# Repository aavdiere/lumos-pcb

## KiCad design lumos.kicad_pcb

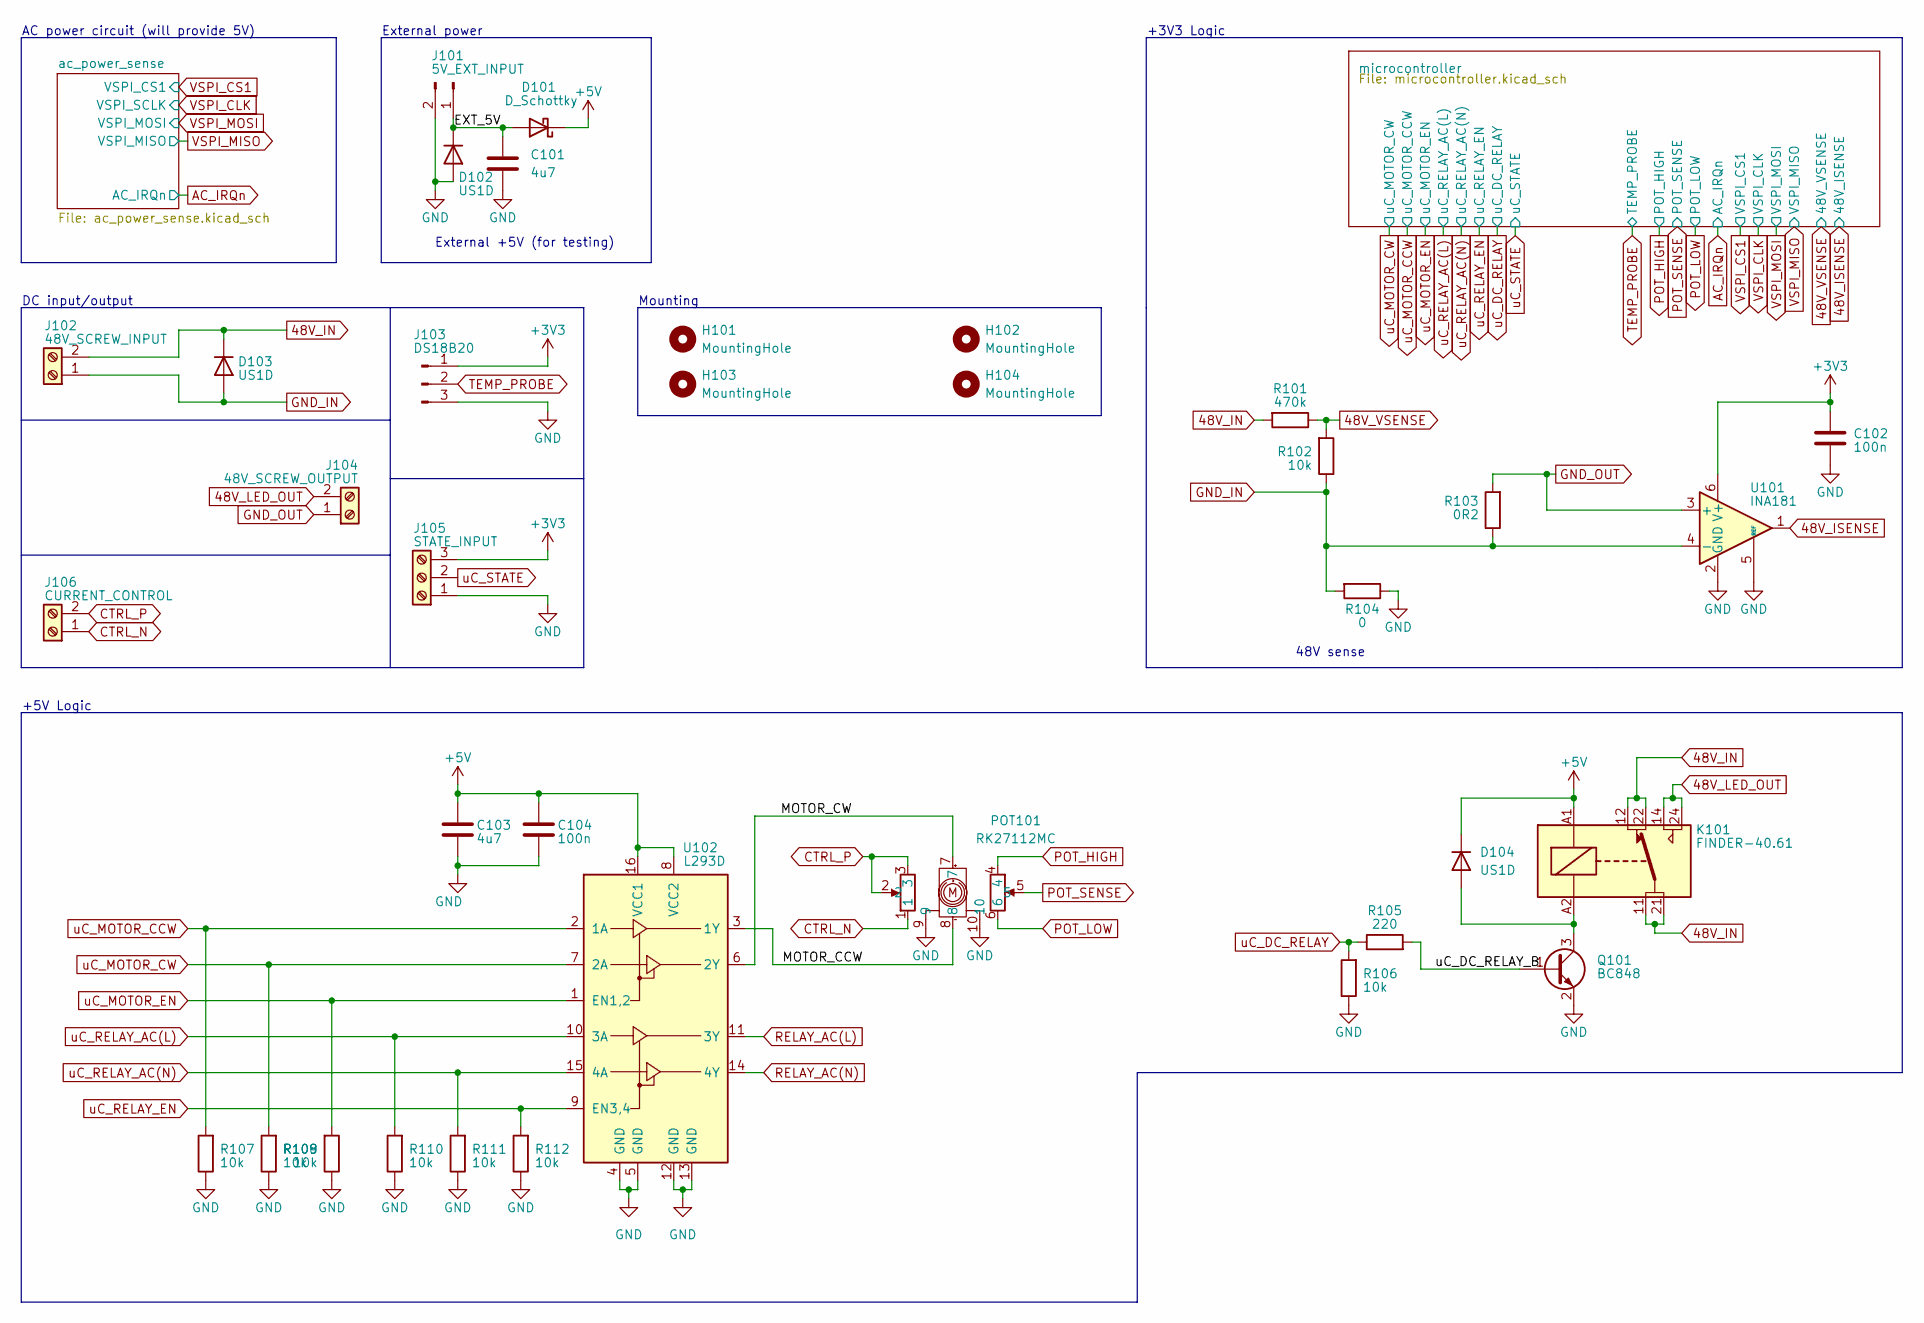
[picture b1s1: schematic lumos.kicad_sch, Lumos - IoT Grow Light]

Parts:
C101, C103: 4u7; C_0402_1005Metric
C102, C104: 100n; C_0402_1005Metric
D101: D_Schottky; D_SOD-523
D102, D103, D104: US1D; D_SMA
H101, H102, H103, H104: MountingHole; MountingHole_3.2mm_M3
J101: 5V_EXT_INPUT; PinHeader_1x02_P2.54mm_Vertical
J102: 48V_SCREW_INPUT; TerminalBlock_Phoenix_MKDS-1,5-2-5.08_1x02_P5.08mm_Horizont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
J103: DS18B20; PinHeader_1x03_P2.54mm_Vertical
J104: 48V_SCREW_OUTPUT; TerminalBlock_Phoenix_MKDS-1,5-2-5.08_1x02_P5.08mm_Horizont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
J105: STATE_INPUT; TerminalBlock_Phoenix_MKDS-1,5-3-5.08_1x03_P5.08mm_Horizont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
J106: CURRENT_CONTROL; TerminalBlock_Phoenix_MKDS-1,5-2-5.08_1x02_P5.08mm_Horizont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
K101: FINDER-40.61; Relay_DPDT_Finder_40.52
POT101: RK27112MC
Q101: BC848; SOT-23
R101: 470k; R_0402_1005Metric
R102, R106, R107, R108, R109, R110, R111, R112: 10k; R_0402_1005Metric
R103: 0R2; R_2512_6332Metric; JLCPCB Part C309535
R104: 0; R_0402_1005Metric
R105: 220; R_0402_1005Metric
U101: INA181; SOT-23-6; JLCPCB Part C2058784
U102: L293D; DIP-16_W7.62mm

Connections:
48V_IN: D103.1 (K), J102.2, K101.11, K101.12, K101.21, K101.22, R101.2
48V_ISENSE: U101.1; also elsewhere on the board
48V_LED_OUT: J104.2, K101.14, K101.24
48V_VSENSE: R101.1, R102.2; also elsewhere on the board
+3V3: C102.1, J103.1, J105.3, U101.6 (V+); also elsewhere on the board
+5V: C103.1, C104.1, D101.1 (K), D104.1 (K), K101.A1, U102.8 (VCC2), U102.16 (VCC1); also elsewhere on the board
/EXT_5V: C101.1, D101.2 (A), D102.1 (K), J101.1
/MOTOR_CCW: POT101.8, U102.3 (1Y)
/MOTOR_CW: POT101.7, U102.6 (2Y)
/uC_DC_RELAY_B: Q101.1 (B), R105.2
CTRL_N: J106.1, POT101.1
CTRL_P: J106.2, POT101.2, POT101.3
GND: C101.2, C102.2, C103.2, C104.2, D102.2 (A), J101.2, J103.3, J105.1, POT101.9, POT101.10, Q101.2 (E), R104.1, R106.1, R107.1, R108.1, R109.1, R110.1, R111.1, R112.1, U101.2 (GND), U101.5 (REF), U102.4 (GND), U102.5 (GND), U102.12 (GND), U102.13 (GND); also elsewhere on the board
GND_IN: D103.2 (A), J102.1, R102.1, R103.1, R104.2, U101.4 (-)
GND_OUT: J104.1, R103.2, U101.3 (+)
unnamed: D104.2 (A), K101.A2, Q101.3 (C)
POT_HIGH: POT101.4; also elsewhere on the board
POT_LOW: POT101.6; also elsewhere on the board
POT_SENSE: POT101.5; also elsewhere on the board
RELAY_AC(L): U102.11 (3Y); also elsewhere on the board
RELAY_AC(N): U102.14 (4Y); also elsewhere on the board
TEMP_PROBE: J103.2; also elsewhere on the board
uC_DC_RELAY: R105.1, R106.2; also elsewhere on the board
uC_MOTOR_CCW: R107.2, U102.2 (1A); also elsewhere on the board
uC_MOTOR_CW: R108.2, U102.7 (2A); also elsewhere on the board
uC_MOTOR_EN: R109.2, U102.1 (EN1,2); also elsewhere on the board
uC_RELAY_AC(L): R110.2, U102.10 (3A); also elsewhere on the board
uC_RELAY_AC(N): R111.2, U102.15 (4A); also elsewhere on the board
uC_RELAY_EN: R112.2, U102.9 (EN3,4); also elsewhere on the board
uC_STATE: J105.2; also elsewhere on the board

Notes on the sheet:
AC power circuit (will provide 5V)
+5V Logic
External +5V (for testing)
+3V3 Logic
48V sense
DC input/output
Mounting
External power

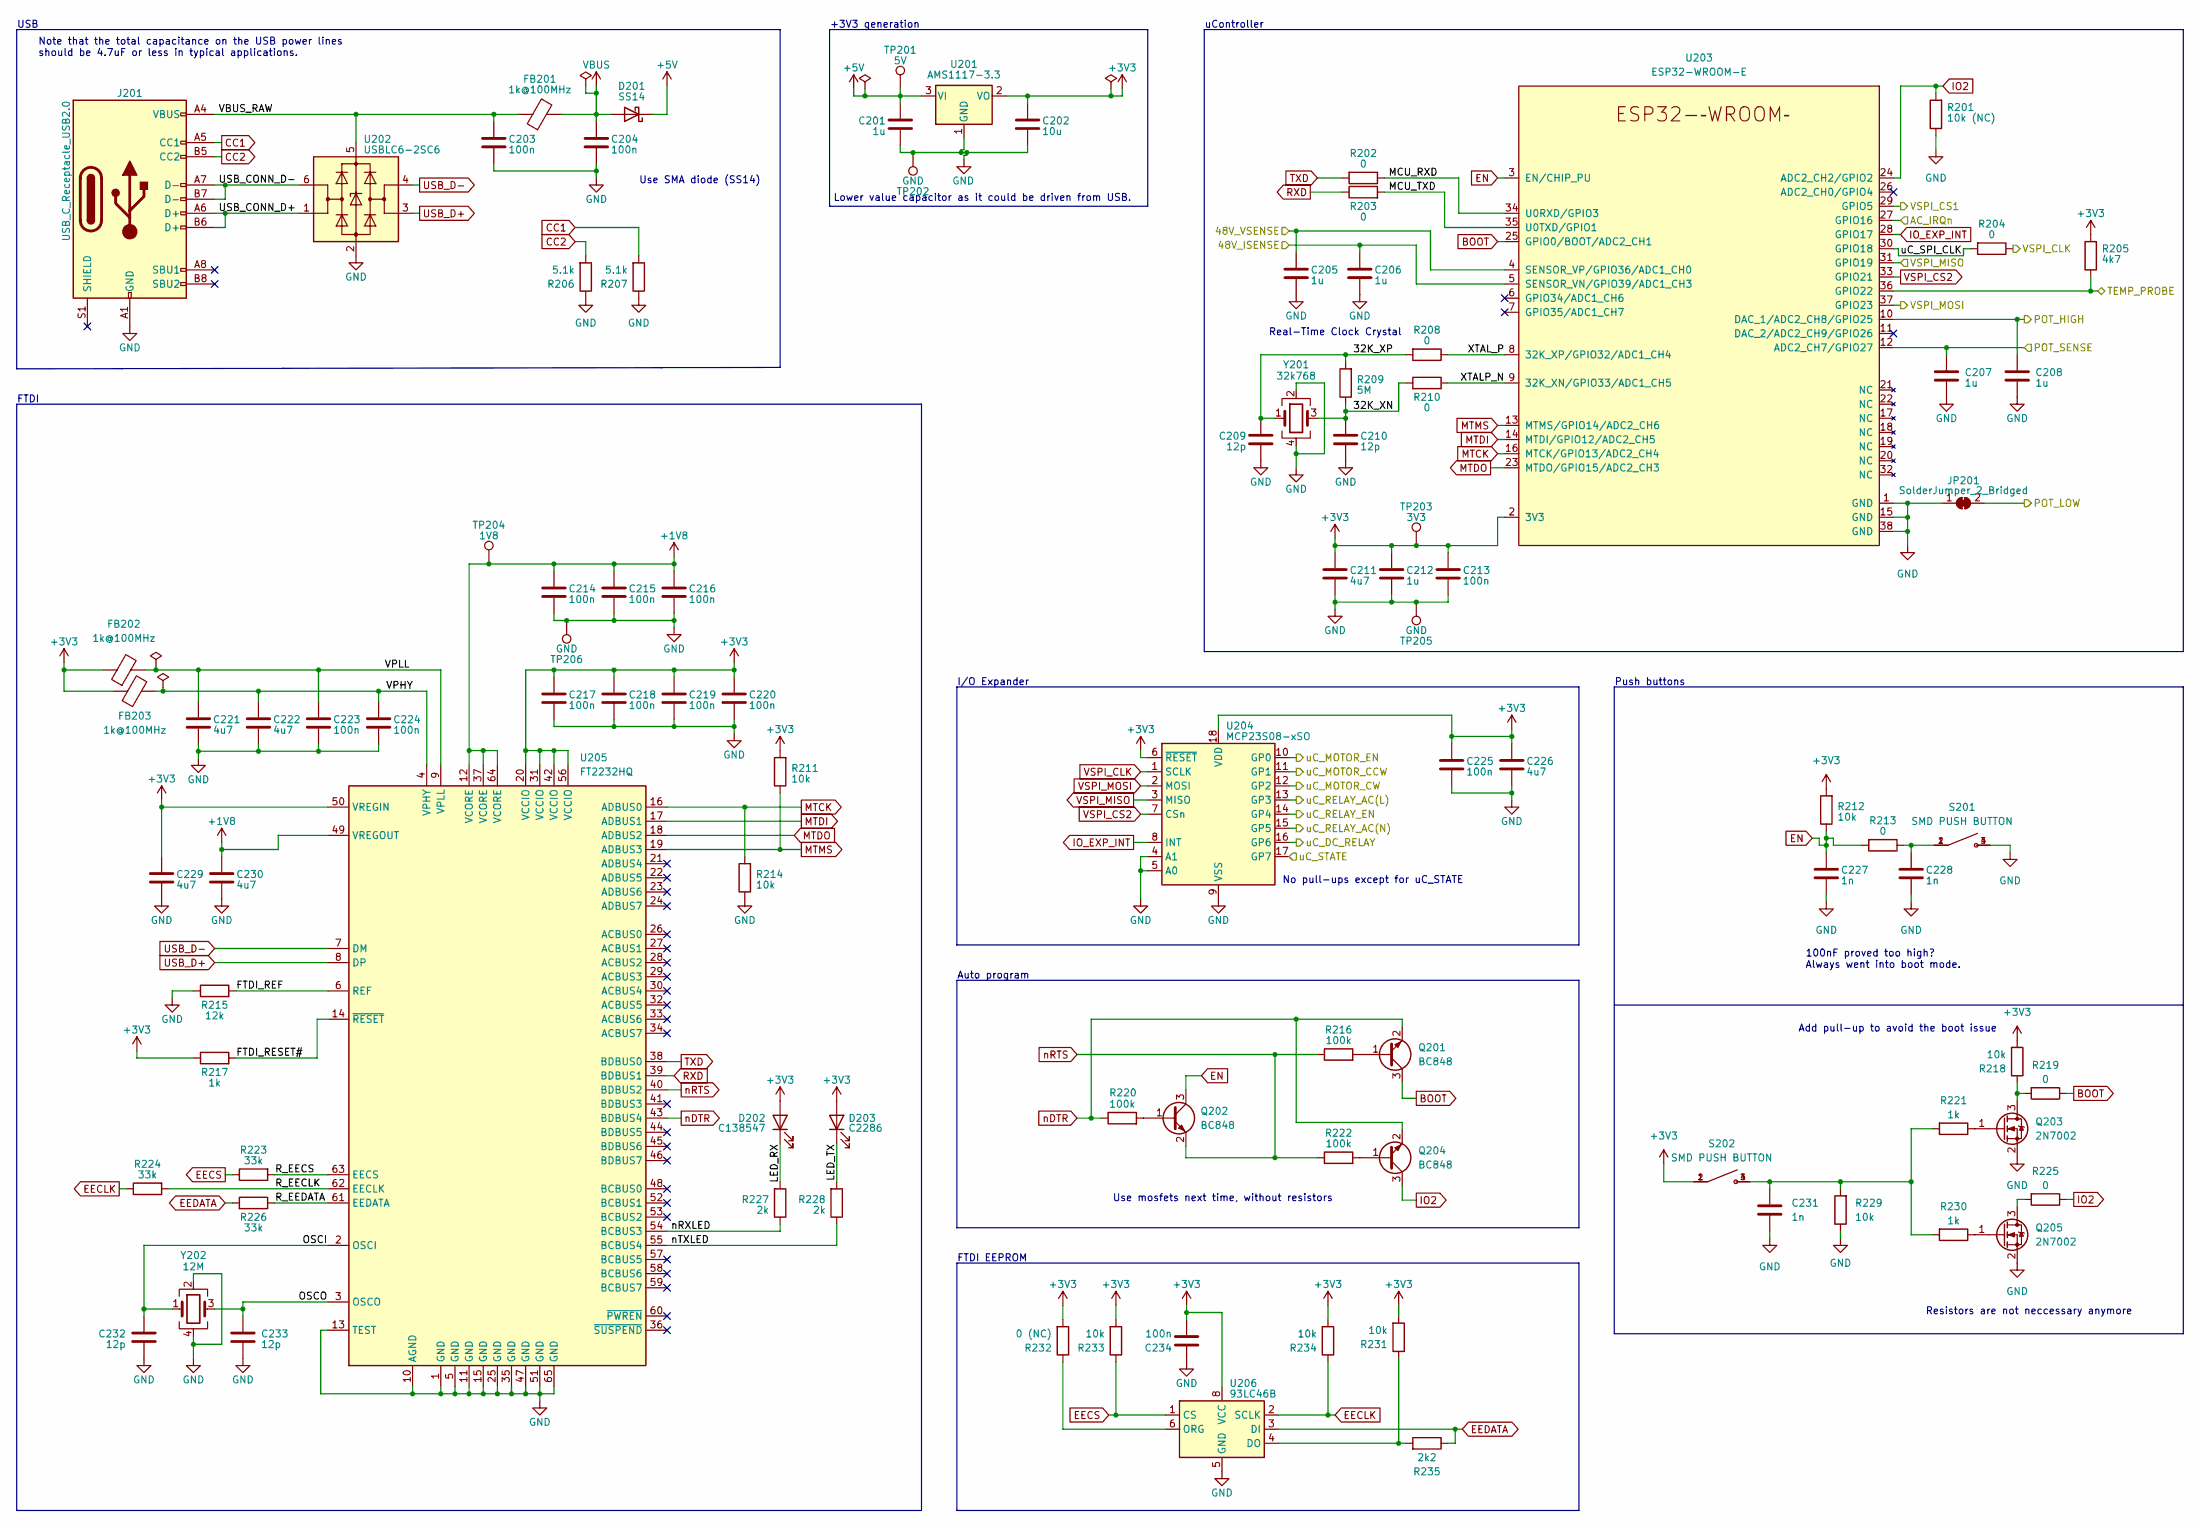
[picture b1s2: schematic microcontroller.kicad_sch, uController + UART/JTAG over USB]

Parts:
C201, C205, C206, C207, C208, C212: 1u; C_0402_1005Metric
C202: 10u; C_0402_1005Metric
C203, C204, C213, C214, C215, C216, C217, C218, C219, C220, C223, C224, C225, C234: 100n; C_0402_1005Metric
C209, C210, C232, C233: 12p; C_0402_1005Metric
C211, C221, C222, C226, C229, C230: 4u7; C_0402_1005Metric
C227, C228, C231: 1n; C_0402_1005Metric
D201: SS14; D_SOD-523
D202: C138547; LED_0603_1608Metric
D203: C2286; LED_0603_1608Metric
FB201, FB202, FB203: 1k@100MHz; L_0402_1005Metric
J201: USB_C_Receptacle_USB2.0; USB_C_Receptacle_HRO_TYPE-C-31-M-12; JLCPCB Part C165948
JP201: SolderJumper_2_Bridged; SolderJumper-2_P1.3mm_Bridged2Bar_Pad1.0x1.5mm
Q201, Q202, Q204: BC848; SOT-23
Q203, Q205: 2N7002; SOT-23
R201: 10k (NC); R_0402_1005Metric
R202, R203, R204, R208, R210, R213, R219, R225: 0; R_0402_1005Metric
R205: 4k7; R_0402_1005Metric
R206, R207: 5.1k; R_0402_1005Metric
R209: 5M; R_0402_1005Metric
R211, R212, R214, R218, R229, R231, R233, R234: 10k; R_0402_1005Metric
R215: 12k; R_0402_1005Metric
R216, R220, R222: 100k; R_0402_1005Metric
R217, R221, R230: 1k; R_0402_1005Metric
R223, R224, R226: 33k; R_0402_1005Metric
R227, R228: 2k; R_0402_1005Metric
R232: 0 (NC); R_0402_1005Metric
R235: 2k2; R_0402_1005Metric
S201, S202: SMD PUSH BUTTON; SW_2-1437565-9; PARTREV V
TP201: 5V; TestPoint_Pad_D2.0mm
TP202, TP205, TP206: GND; TestPoint_Pad_D2.0mm
TP203: 3V3; TestPoint_Pad_D2.0mm
TP204: 1V8; TestPoint_Pad_D2.0mm
U201: AMS1117-3.3; SOT-223-3_TabPin2
U202: USBLC6-2SC6; SOT-23-6; JLCPCB Part C7519
U203: ESP32-WROOM-E; ESP32-WROOM-32E; JLCPCB Part C701341
U204: MCP23S08-xSO; SOIC-18W_7.5x11.6mm_P1.27mm
U205: FT2232HQ; QFN-64-1EP_9x9mm_P0.5mm_EP4.35x4.35mm; JLCPCB Part C193662
U206: 93LC46B; SOIC-8_3.9x4.9mm_P1.27mm; JLCPCB Part C16253
Y201: 32k768; Crystal_SMD_5032-4Pin_5.0x3.2mm; JLCPCB Part C390448
Y202: 12M; Crystal_SMD_5032-4Pin_5.0x3.2mm; JLCPCB Part C390438

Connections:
48V_ISENSE: C206.1, U203.5 (SENSOR_VN/GPIO39/ADC1_CH3); also elsewhere on the board
48V_VSENSE: C205.1, U203.4 (SENSOR_VP/GPIO36/ADC1_CH0); also elsewhere on the board
+1V8: C214.1, C215.1, C216.1, C230.1, TP204.1, U205.12 (VCORE), U205.37 (VCORE), U205.49 (VREGOUT), U205.64 (VCORE)
+3V3: C202.1, C211.1, C212.1, C213.1, C217.1, C218.1, C219.1, C220.1, C225.1, C226.1, C229.1, C234.2, D202.2 (A), D203.2 (A), FB202.1, FB203.1, R205.2, R211.2, R212.2, R217.1, R218.2, R231.2, R232.2, R233.2, R234.2, S202.1, S202.2, TP203.1, U201.2 (VO), U203.2 (3V3), U204.6 (~RESET), U204.18 (VDD), U205.20 (VCCIO), U205.31 (VCCIO), U205.42 (VCCIO), U205.50 (VREGIN), U205.56 (VCCIO), U206.8 (VCC); also elsewhere on the board
+5V: C201.1, D201.1 (K), TP201.1, U201.3 (VI); also elsewhere on the board
/microcontroller/32K_XN: C210.1, R209.1, R210.2, Y201.3
/microcontroller/32K_XP: C209.2, R208.2, R209.2, Y201.1
/microcontroller/FTDI_REF: R215.2, U205.6 (REF)
/microcontroller/FTDI_RESET#: R217.2, U205.14 (~RESET)
/microcontroller/LED_RX: D202.1 (K), R227.2
/microcontroller/LED_TX: D203.1 (K), R228.2
/microcontroller/MCU_RXD: R202.1, U203.34 (U0RXD/GPIO3)
/microcontroller/MCU_TXD: R203.2, U203.35 (U0TXD/GPIO1)
/microcontroller/OSCI: C232.2, U205.2 (OSCI), Y202.1
/microcontroller/OSCO: C233.1, U205.3 (OSCO), Y202.3
/microcontroller/R_EECLK: R224.2, U205.62 (EECLK)
/microcontroller/R_EECS: R223.2, U205.63 (EECS)
/microcontroller/R_EEDATA: R226.1, U205.61 (EEDATA)
/microcontroller/USB_CONN_D+: J201.A6 (D+), J201.B6 (D+), U202.1 (I/O1)
/microcontroller/USB_CONN_D-: J201.A7 (D-), J201.B7 (D-), U202.6 (I/O1)
/microcontroller/VBUS_RAW: C203.1, FB201.1, J201.A4 (VBUS), J201.A9 (VBUS), J201.B4 (VBUS), J201.B9 (VBUS), U202.5 (VBUS)
/microcontroller/VPHY: C222.1, C224.1, FB203.2, U205.4 (VPHY)
/microcontroller/VPLL: C221.1, C223.1, FB202.2, U205.9 (VPLL)
/microcontroller/XTALP_N: R210.1, U203.9 (32K_XN/GPIO33/ADC1_CH5)
/microcontroller/XTAL_P: R208.1, U203.8 (32K_XP/GPIO32/ADC1_CH4)
/microcontroller/nRXLED: R227.1, U205.54 (BCBUS3)
/microcontroller/nTXLED: R228.1, U205.55 (BCBUS4)
/microcontroller/uC_SPI_CLK: R204.2, U203.30 (GPIO18)
AC_IRQn: U203.27 (GPIO16); also elsewhere on the board
BOOT: Q201.3 (C), R219.1, U203.25 (GPIO0/BOOT/ADC2_CH1)
CC1: J201.A5 (CC1), R207.2
CC2: J201.B5 (CC2), R206.2
EECLK: R224.1, R234.1, U206.2 (SCLK)
EECS: R223.1, R233.1, U206.1 (CS)
EEDATA: R226.2, R235.1, U206.3 (DI)
EN: C227.1, Q202.3 (C), R212.1, R213.2, U203.3 (EN/CHIP_PU)
GND: C201.2, C202.2, C203.2, C204.2, C205.2, C206.2, C207.2, C208.2, C209.1, C210.2, C211.2, C212.2, C213.2, C214.2, C215.2, C216.2, C217.2, C218.2, C219.2, C220.2, C221.2, C222.2, C223.2, C224.2, C225.2, C226.2, C227.2, C228.2, C229.2, C230.2, C231.2, C232.1, C233.2, C234.1, J201.A1 (GND), J201.A12 (GND), J201.B1 (GND), J201.B12 (GND), JP201.1 (A), Q203.2 (S), Q205.2 (S), R201.1, R206.1, R207.1, R214.1, R215.1, R229.1, S201.3, S201.4, TP202.1, TP205.1, TP206.1, U201.1 (GND), U202.2 (GND), U203.1 (GND), U203.15 (GND), U203.38 (GND), U204.4 (A1), U204.5 (A0), U204.9 (VSS), U205.1 (GND), U205.5 (GND), U205.10 (AGND), U205.11 (GND), U205.13 (TEST), U205.15 (GND), U205.25 (GND), U205.35 (GND), U205.47 (GND), U205.51 (GND), U205.65 (GND), U206.5 (GND), Y201.2, Y201.4, Y202.2, Y202.4; also elsewhere on the board
IO2: Q204.3 (C), R201.2, R225.1, U203.24 (ADC2_CH2/GPIO2)
IO_EXP_INT: U203.28 (GPIO17), U204.8 (INT)
MTCK: R214.2, U203.16 (MTCK/GPIO13/ADC2_CH4), U205.16 (ADBUS0)
MTDI: U203.14 (MTDI/GPIO12/ADC2_CH5), U205.17 (ADBUS1)
MTDO: U203.23 (MTDO/GPIO15/ADC2_CH3), U205.18 (ADBUS2)
MTMS: R211.1, U203.13 (MTMS/GPIO14/ADC2_CH6), U205.19 (ADBUS3)
unnamed: C228.1, R213.1, S201.1, S201.2
unnamed: C231.1, R221.2, R229.2, R230.2, S202.3, S202.4
unnamed: Q201.1 (B), R216.2
unnamed: Q202.1 (B), R220.2
unnamed: Q203.1 (G), R221.1
unnamed: Q203.3 (D), R218.1, R219.2
unnamed: Q204.1 (B), R222.2
unnamed: Q205.1 (G), R230.1
unnamed: Q205.3 (D), R225.2
unnamed: R231.1, R235.2, U206.4 (DO)
unnamed: R232.1, U206.6 (ORG)
POT_HIGH: C208.1, U203.10 (DAC_1/ADC2_CH8/GPIO25); also elsewhere on the board
POT_LOW: JP201.2 (B); also elsewhere on the board
POT_SENSE: C207.1, U203.12 (ADC2_CH7/GPIO27); also elsewhere on the board
RXD: R203.1, U205.39 (BDBUS1)
TEMP_PROBE: R205.1, U203.36 (GPIO22); also elsewhere on the board
TXD: R202.2, U205.38 (BDBUS0)
USB_D+: U202.3 (I/O2), U205.8 (DP)
USB_D-: U202.4 (I/O2), U205.7 (DM)
VBUS: C204.1, D201.2 (A), FB201.2
VSPI_CLK: R204.1, U204.1 (SCLK); also elsewhere on the board
VSPI_CS1: U203.29 (GPIO5); also elsewhere on the board
VSPI_CS2: U203.33 (GPIO21), U204.7 (CSn)
VSPI_MISO: U203.31 (GPIO19), U204.3 (MISO); also elsewhere on the board
VSPI_MOSI: U203.37 (GPIO23), U204.2 (MOSI); also elsewhere on the board
nDTR: Q201.2 (E), Q204.2 (E), R220.1, U205.43 (BDBUS4)
nRTS: Q202.2 (E), R216.1, R222.1, U205.40 (BDBUS2)
uC_DC_RELAY: U204.16 (GP6); also elsewhere on the board
uC_MOTOR_CCW: U204.11 (GP1); also elsewhere on the board
uC_MOTOR_CW: U204.12 (GP2); also elsewhere on the board
uC_MOTOR_EN: U204.10 (GP0); also elsewhere on the board
uC_RELAY_AC(L): U204.13 (GP3); also elsewhere on the board
uC_RELAY_AC(N): U204.15 (GP5); also elsewhere on the board
uC_RELAY_EN: U204.14 (GP4); also elsewhere on the board
uC_STATE: U204.17 (GP7); also elsewhere on the board

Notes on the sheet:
I/O Expander
Push buttons
FTDI
Note that the total capacitance on the USB power lines should be 4.7uF or less in typical applications.
No pull-ups except for uC_STATE
uController
Real-Time Clock Crystal
Add pull-up to avoid the boot issue
Auto program
Use SMA diode (SS14)
Resistors are not neccessary anymore
Use mosfets next time, without resistors
FTDI EEPROM
Lower value capacitor as it could be driven from USB.
100nF proved too high? Always went into boot mode.
USB
+3V3 generation

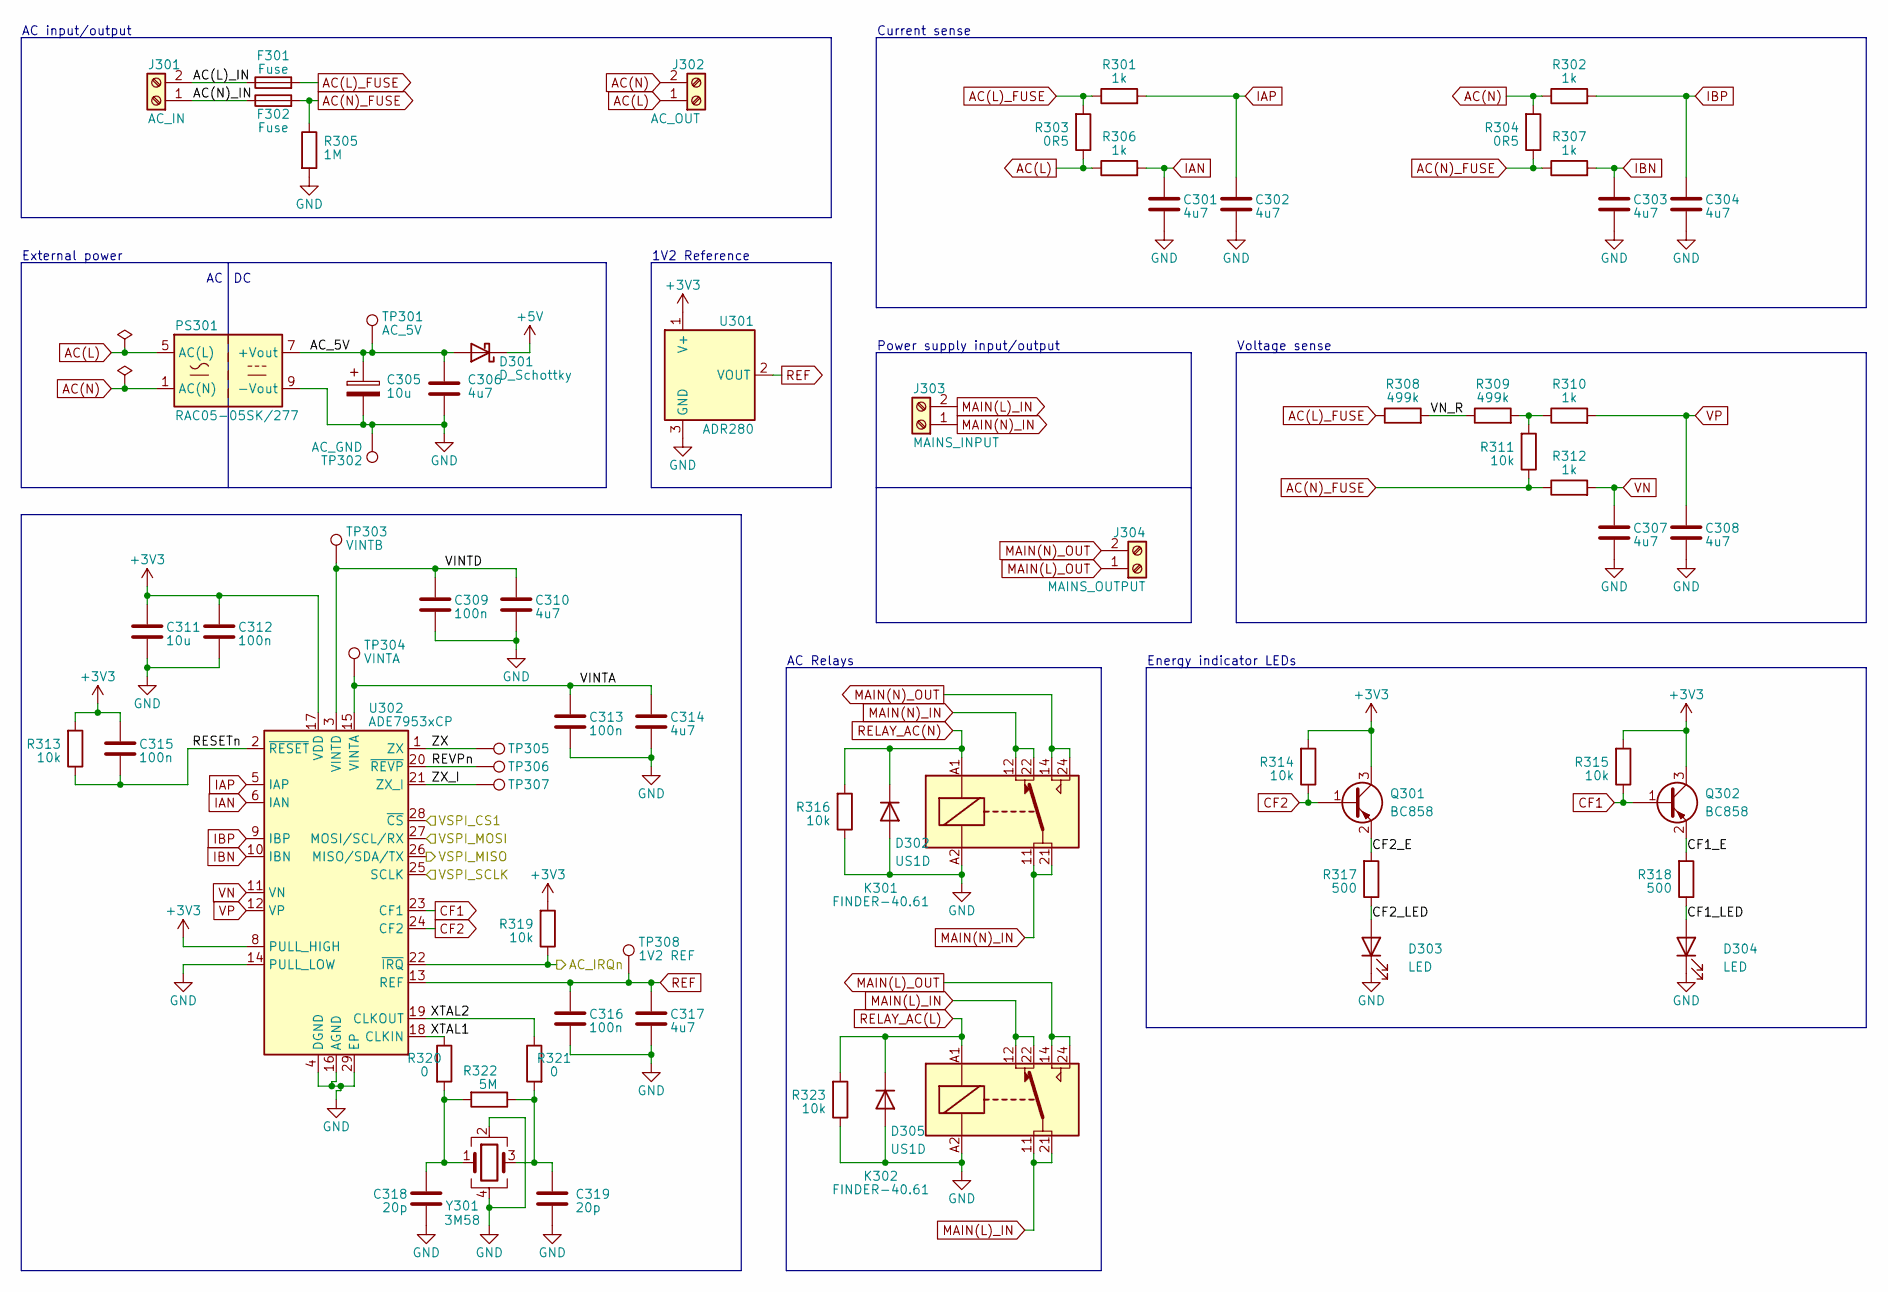
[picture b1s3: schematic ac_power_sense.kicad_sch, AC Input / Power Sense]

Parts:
C301, C302, C303, C304, C306, C307, C308, C310, C314, C317: 4u7; C_0402_1005Metric
C305, C311: 10u; C_0402_1005Metric
C309, C312, C313, C315, C316: 100n; C_0402_1005Metric
C318, C319: 20p; C_0402_1005Metric
D301: D_Schottky; D_SOD-523
D302, D305: US1D; D_SMA
D303, D304: LED; LED_0603_1608Metric_Pad1.05x0.95mm_HandSolder
F301, F302: Fuse; Fuseholder_Cylinder-5x20mm_Schurter_0031_8201_Horizontal_Op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
J301: AC_IN; TerminalBlock_Phoenix_MKDS-1,5-2-5.08_1x02_P5.08mm_Horizont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
J302: AC_OUT; TerminalBlock_Phoenix_MKDS-1,5-2-5.08_1x02_P5.08mm_Horizont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
J303: MAINS_INPUT; TerminalBlock_Phoenix_MKDS-1,5-2-5.08_1x02_P5.08mm_Horizont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
J304: MAINS_OUTPUT; TerminalBlock_Phoenix_MKDS-1,5-2-5.08_1x02_P5.08mm_Horizont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
K301, K302: FINDER-40.61; Relay_DPDT_Finder_40.52
PS301: RAC05-05SK/277; RECOM_RAC05-xxSK-277
Q301, Q302: BC858; SOT-23
R301, R302, R306, R307, R310, R312: 1k; R_0402_1005Metric
R303, R304: 0R5; R_2512_6332Metric
R305: 1M; R_0805_2012Metric
R308, R309: 499k; R_0805_2012Metric
R311: 10k; R_0805_2012Metric
R313, R314, R315, R316, R319, R323: 10k; R_0402_1005Metric
R317, R318: 500; R_0402_1005Metric
R320, R321: 0; R_0402_1005Metric
R322: 5M; R_0402_1005Metric
TP301: AC_5V; TestPoint_Pad_D2.0mm
TP302: AC_GND; TestPoint_Pad_D2.0mm
TP303: VINTB; TestPoint_Pad_D2.0mm
TP304: VINTA; TestPoint_Pad_D2.0mm
TP305: ZX; TestPoint_Pad_D2.0mm
TP306: REVPn; TestPoint_Pad_D2.0mm
TP307: ZX_I; TestPoint_Pad_D2.0mm
TP308: 1V2 REF; TestPoint_Pad_D2.0mm
U301: ADR280; SOT-23; JLCPCB Part C2156560
U302: ADE7953xCP; LFCSP-28-1EP_5x5mm_P0.5mm_EP3.14x3.14mm; JLCPCB Part C515890
Y301: 3M58; Crystal_SMD_5032-4Pin_5.0x3.2mm

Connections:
+3V3: C311.1, C312.1, C315.1, Q301.3 (C), Q302.3 (C), R313.2, R314.2, R315.2, R319.2, U301.1 (V+), U302.7 (PULL_HIGH), U302.8 (PULL_HIGH), U302.17 (VDD); also elsewhere on the board
+5V: D301.1 (K); also elsewhere on the board
/ac_power_sense/AC(L)_IN: F301.1, J301.2
/ac_power_sense/AC(N)_IN: F302.1, J301.1
/ac_power_sense/AC_5V: C305.1, C306.1, D301.2 (A), PS301.7 (+Vout), TP301.1
/ac_power_sense/CF1_E: Q302.2 (E), R318.2
/ac_power_sense/CF1_LED: D304.2 (A), R318.1
/ac_power_sense/CF2_E: Q301.2 (E), R317.2
/ac_power_sense/CF2_LED: D303.2 (A), R317.1
/ac_power_sense/RESETn: C315.2, R313.1, U302.2 (~RESET)
/ac_power_sense/REVPn: TP306.1, U302.20 (~REVP)
/ac_power_sense/VINTA: C313.1, C314.1, TP304.1, U302.15 (VINTA)
/ac_power_sense/VINTD: C309.1, C310.1, TP303.1, U302.3 (VINTD)
/ac_power_sense/VN_R: R308.2, R309.1
/ac_power_sense/XTAL1: R320.1, U302.18 (CLKIN)
/ac_power_sense/XTAL2: R321.1, U302.19 (CLKOUT)
/ac_power_sense/ZX: TP305.1, U302.1 (ZX)
/ac_power_sense/ZX_I: TP307.1, U302.21 (ZX_I)
AC(L): J302.1, PS301.5 (AC(L)), R303.1, R306.1
AC(L)_FUSE: F301.2, R301.1, R303.2, R308.1
AC(N): J302.2, PS301.1 (AC(N)), R302.1, R304.2
AC(N)_FUSE: F302.2, R304.1, R305.1, R307.1, R311.1, R312.1
AC_IRQn: R319.1, U302.22 (~IRQ); also elsewhere on the board
CF1: Q302.1 (B), R315.1, U302.23 (CF1)
CF2: Q301.1 (B), R314.1, U302.24 (CF2)
GND: C301.2, C302.2, C303.2, C304.2, C305.2, C306.2, C307.2, C308.2, C309.2, C310.2, C311.2, C312.2, C313.2, C314.2, C316.2, C317.2, C318.1, C319.2, D302.2 (A), D303.1 (K), D304.1 (K), D305.2 (A), K301.A2, K302.A2, PS301.9 (-Vout), R305.2, R316.1, R323.1, TP302.1, U301.3 (GND), U302.4 (DGND), U302.14 (PULL_LOW), U302.16 (AGND), U302.29 (EP), Y301.2, Y301.4; also elsewhere on the board
IAN: C301.1, R306.2, U302.6 (IAN)
IAP: C302.1, R301.2, U302.5 (IAP)
IBN: C303.1, R307.2, U302.10 (IBN)
IBP: C304.1, R302.2, U302.9 (IBP)
MAIN(L)_IN: J303.2, K302.11, K302.12, K302.21, K302.22
MAIN(L)_OUT: J304.1, K302.14, K302.24
MAIN(N)_IN: J303.1, K301.11, K301.12, K301.21, K301.22
MAIN(N)_OUT: J304.2, K301.14, K301.24
unnamed: C318.2, R320.2, R322.2, Y301.1
unnamed: C319.1, R321.2, R322.1, Y301.3
unnamed: R309.2, R310.1, R311.2
REF: C316.1, C317.1, TP308.1, U301.2 (VOUT), U302.13 (REF)
RELAY_AC(L): D305.1 (K), K302.A1, R323.2; also elsewhere on the board
RELAY_AC(N): D302.1 (K), K301.A1, R316.2; also elsewhere on the board
VN: C307.1, R312.2, U302.11 (VN)
VP: C308.1, R310.2, U302.12 (VP)
VSPI_CLK: U302.25 (SCLK); also elsewhere on the board
VSPI_CS1: U302.28 (~CS); also elsewhere on the board
VSPI_MISO: U302.26 (MISO/SDA/TX); also elsewhere on the board
VSPI_MOSI: U302.27 (MOSI/SCL/RX); also elsewhere on the board

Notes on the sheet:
AC Relays
Energy indicator LEDs
Power supply input/output
Voltage sense
Current sense
1V2 Reference
External power
AC input/output

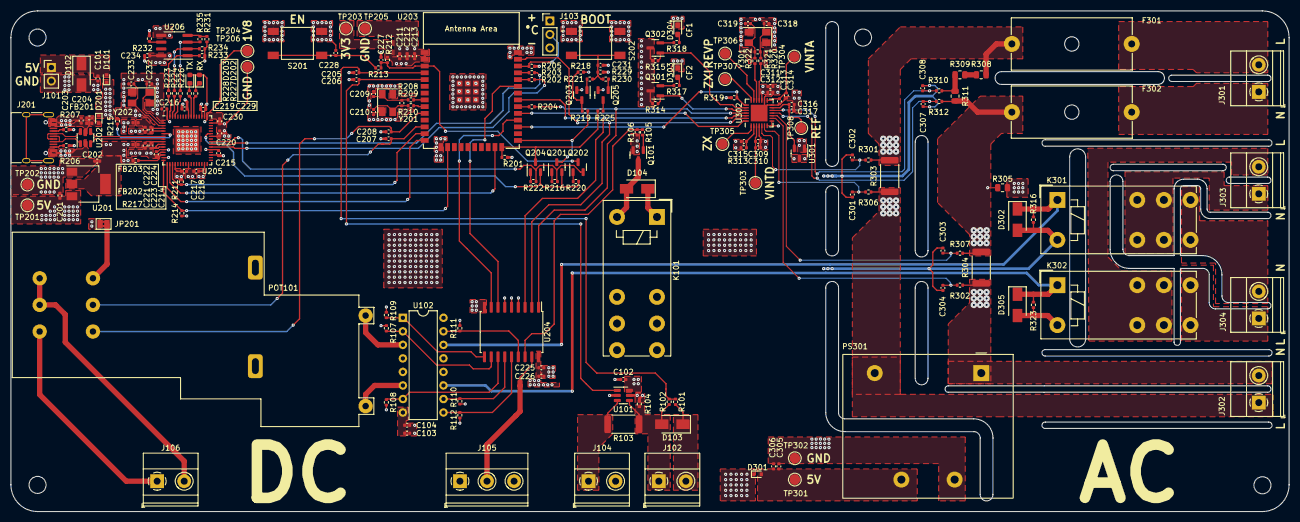
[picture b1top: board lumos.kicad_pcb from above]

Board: 4 copper layers, 240.0 x 94.0 mm, 202 parts (0 on the bottom side), 127 nets.

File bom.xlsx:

Comment | Designator | Footprint | JLCPCB Part #
4u7 | C101, C103, C211, C221, C222, C226, C229, C230, C301-C304, C306-C308, C310, C31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 | Capacitor_SMD:C_0402_1005Metric
100n | C102, C104, C203, C204, C213-C220, C223-C225, C227, C228, C231, C234, C309, C31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 | Capacitor_SMD:C_0402_1005Metric
10u | C202, C311 | Capacitor_SMD:C_0402_1005Metric
1u | C201, C205-C208, C212 | Capacitor_SMD:C_0402_1005Metric
12p | C209, C210, C232, C233 | Capacitor_SMD:C_0402_1005Metric
47u | C305 | Capacitor_SMD:C_0402_1005Metric
20p | C318, C319 | Capacitor_SMD:C_0402_1005Metric
D_Schottky | D101, D201, D202, D301 | Diode_SMD:D_SOD-523
US1D | D102-D104, D302, D305 | Diode_SMD:D_SMA
C138547 | D203 | LED_SMD:LED_0603_1608Metric
C2286 | D204 | LED_SMD:LED_0603_1608Metric
LED | D303, D304 | LED_SMD:LED_0603_1608Metric_Pad1.05x0.95mm_HandSolder
Fuse | F301, F302 | Fuse:Fuseholder_Cylinder-5x20mm_Schurter_0031_8201_Horizontal_Open
1k@100MHz | FB201-FB203 | Inductor_SMD:L_0402_1005Metric
MountingHole | H101-H104 | MountingHole:MountingHole_3.2mm_M3
5V_EXT_INPUT | J101 | Connector_PinHeader_2.54mm:PinHeader_1x02_P2.54mm_Vertical
48V_SCREW_INPUT | J102 | TerminalBlock_Phoenix:TerminalBlock_Phoenix_MKDS-1,5-2-5.08_1x02_P5.08mm_Horizo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
DS18B20 | J103 | Connector_PinHeader_2.54mm:PinHeader_1x03_P2.54mm_Vertical
48V_SCREW_OUTPUT | J104 | TerminalBlock_Phoenix:TerminalBlock_Phoenix_MKDS-1,5-2-5.08_1x02_P5.08mm_Horizo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
STATE_INPUT | J105 | TerminalBlock_Phoenix:TerminalBlock_Phoenix_MKDS-1,5-3-5.08_1x03_P5.08mm_Horizo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
CURRENT_CONTROL | J106 | TerminalBlock_Phoenix:TerminalBlock_Phoenix_MKDS-1,5-2-5.08_1x02_P5.08mm_Horizo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
USB_C_Receptacle_USB2.0 | J201 | Connector_USB:USB_C_Receptacle_HRO_TYPE-C-31-M-12 | C165948
AC_IN | J301 | TerminalBlock_Phoenix:TerminalBlock_Phoenix_MKDS-1,5-2-5.08_1x02_P5.08mm_Horizo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
AC_OUT | J302 | TerminalBlock_Phoenix:TerminalBlock_Phoenix_MKDS-1,5-2-5.08_1x02_P5.08mm_Horizo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
MAINS_INPUT | J303 | TerminalBlock_Phoenix:TerminalBlock_Phoenix_MKDS-1,5-2-5.08_1x02_P5.08mm_Horizo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
MAINS_OUTPUT | J304 | TerminalBlock_Phoenix:TerminalBlock_Phoenix_MKDS-1,5-2-5.08_1x02_P5.08mm_Horizo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
SolderJumper_2_Bridged | JP201 | Jumper:SolderJumper-2_P1.3mm_Bridged2Bar_Pad1.0x1.5mm
FINDER-40.61 | K101, K301, K302 | Relay_THT:Relay_DPDT_Finder_40.52
RK27112MC | POT101 | lumos:RK27112MC
RAC05-05SK/277 | PS301 | lumos:RECOM_RAC05-xxSK-277
BC848 | Q101, Q201, Q202, Q204 | Package_TO_SOT_SMD:SOT-23
2N7002 | Q203, Q205 | Package_TO_SOT_SMD:SOT-23
BC858 | Q301, Q302 | Package_TO_SOT_SMD:SOT-23
470k | R101 | Resistor_SMD:R_0402_1005Metric
0R2 | R103 | Resistor_SMD:R_2512_6332Metric | C309535
0 | R104, R202-R204, R208, R210, R214, R219, R225, R320, R321 | Resistor_SMD:R_0402_1005Metric
220 | R105 | Resistor_SMD:R_0402_1005Metric
10k | R102, R106-R112, R212, R213, R215, R229, R231, R233, R234, R313-R316, R319, R323 | Resistor_SMD:R_0402_1005Metric
10k (NC) | R201 | Resistor_SMD:R_0402_1005Metric
4k7 | R205 | Resistor_SMD:R_0402_1005Metric
5.1k | R206, R207 | Resistor_SMD:R_0402_1005Metric
5M | R209, R322 | Resistor_SMD:R_0402_1005Metric
12k | R216 | Resistor_SMD:R_0402_1005Metric
1k | R218, R221, R230, R301, R302, R306, R307, R310, R312 | Resistor_SMD:R_0402_1005Metric
100k | R217, R220, R222 | Resistor_SMD:R_0402_1005Metric
33k | v R223, R224, R226 | Resistor_SMD:R_0402_1005Metric
2k | R223 | Resistor_SMD:R_0402_1005Metric
0 (NC) | R224 | Resistor_SMD:R_0402_1005Metric
2k2 | R226 | Resistor_SMD:R_0402_1005Metric
0R5 | R227, R228 | Resistor_SMD:R_2512_6332Metric
1M | R232 | Resistor_SMD:R_0805_2012Metric
499k | R235 | Resistor_SMD:R_0805_2012Metric
10k | R303, R304 | Resistor_SMD:R_0805_2012Metric
500 | R305 | Resistor_SMD:R_0402_1005Metric
SMD PUSH BUTTON | R308, R309 | lumos:SW_2-1437565-9
5V | R311 | TestPoint:TestPoint_Pad_D2.0mm
3V3 | R317, R318 | TestPoint:TestPoint_Pad_D2.0mm
1V8 | S201, S202 | TestPoint:TestPoint_Pad_D2.0mm
GND | TP201 | TestPoint:TestPoint_Pad_D2.0mm
AC_5V | TP203 | TestPoint:TestPoint_Pad_D2.0mm
VINTB | TP204 | TestPoint:TestPoint_Pad_D2.0mm
VINTA | TP202, TP205, TP206 | TestPoint:TestPoint_Pad_D2.0mm
ZX | TP301 | TestPoint:TestPoint_Pad_D2.0mm
REVPn | TP302 | TestPoint:TestPoint_Pad_D2.0mm
ZX_I | TP303 | TestPoint:TestPoint_Pad_D2.0mm
1V2 REF | TP304 | TestPoint:TestPoint_Pad_D2.0mm
AC_GND | TP305 | TestPoint:TestPoint_Pad_D2.0mm
INA181 | TP306 | Package_TO_SOT_SMD:SOT-23-6
L293D | TP307 | Package_DIP:DIP-16_W7.62mm
AMS1117-3.3 | TP308 | Package_TO_SOT_SMD:SOT-223-3_TabPin2
USBLC6-2SC6 | U101 | Package_TO_SOT_SMD:SOT-23-6 | C2058784
ESP32-WROOM-E | U102 | lumos:ESP32-WROOM-32E
MCP23S08-xSO | U201 | Package_SO:SOIC-18W_7.5x11.6mm_P1.27mm
FT2232HQ | U202 | lumos:QFN-64-1EP_9x9mm_P0.5mm_EP4.35x4.35mm | C7519
93LC46B | U203 | Package_SO:SOIC-8_3.9x4.9mm_P1.27mm | C701341
ADR280 | U204 | Package_TO_SOT_SMD:SOT-23
ADE7953xCP | U205 | Package_CSP:LFCSP-28-1EP_5x5mm_P0.5mm_EP3.14x3.14mm | C193662
32k768 | U206 | lumos:Crystal_SMD_5032-4Pin_5.0x3.2mm | C16253
12M | U301 | lumos:Crystal_SMD_5032-4Pin_5.0x3.2mm | C2156560
3M58 | U302 | lumos:Crystal_SMD_5032-4Pin_5.0x3.2mm | C515890
 | Y201 |  | C390448
 | Y202 |  | C390438
 | Y301

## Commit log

2023-01-25 Final pcb already
